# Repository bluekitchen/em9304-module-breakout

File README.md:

# Breakout Board for the EM9304 Module

The EM9304 module from the DVK has a 16-pin 0.05" header. To make it easier to connect it with jumper wires or plug it into a solderless breadboard, we've created a simple breakout board.

It is can be directly [ordered at OSHpark](https://oshpark.com/shared_projects/6OCoIZie)

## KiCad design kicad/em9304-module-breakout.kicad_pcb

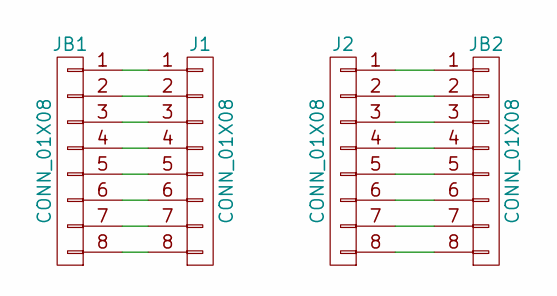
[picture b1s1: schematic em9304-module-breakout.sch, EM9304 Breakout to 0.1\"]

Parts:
J1, J2: CONN_01X08; Socket_Strip_Straight_1x08_Pitch1.27mm
JB1, JB2: CONN_01X08; Pin_Header_Straight_1x08_Pitch2.54mm

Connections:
unnamed: J1.1, JB1.1
unnamed: J1.2, JB1.2
unnamed: J1.3, JB1.3
unnamed: J1.4, JB1.4
unnamed: J1.5, JB1.5
unnamed: J1.6, JB1.6
unnamed: J1.7, JB1.7
unnamed: J1.8, JB1.8
unnamed: J2.1, JB2.1
unnamed: J2.2, JB2.2
unnamed: J2.3, JB2.3
unnamed: J2.4, JB2.4
unnamed: J2.5, JB2.5
unnamed: J2.6, JB2.6
unnamed: J2.7, JB2.7
unnamed: J2.8, JB2.8

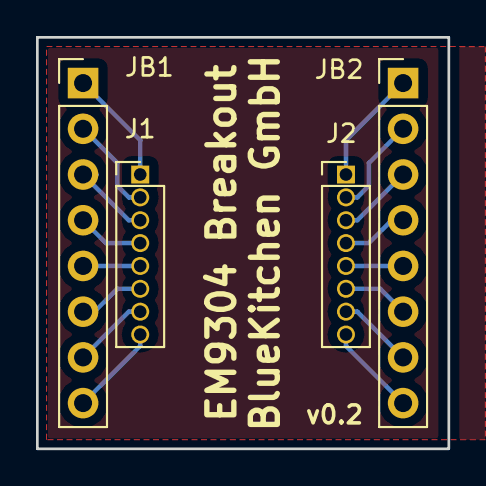
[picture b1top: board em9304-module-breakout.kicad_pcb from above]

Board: 2 copper layers, 22.9 x 22.9 mm, 4 parts (0 on the bottom side), 16 nets.
